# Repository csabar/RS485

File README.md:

# RS485
MAX485 breakout board which fits Arduino Pro Mini

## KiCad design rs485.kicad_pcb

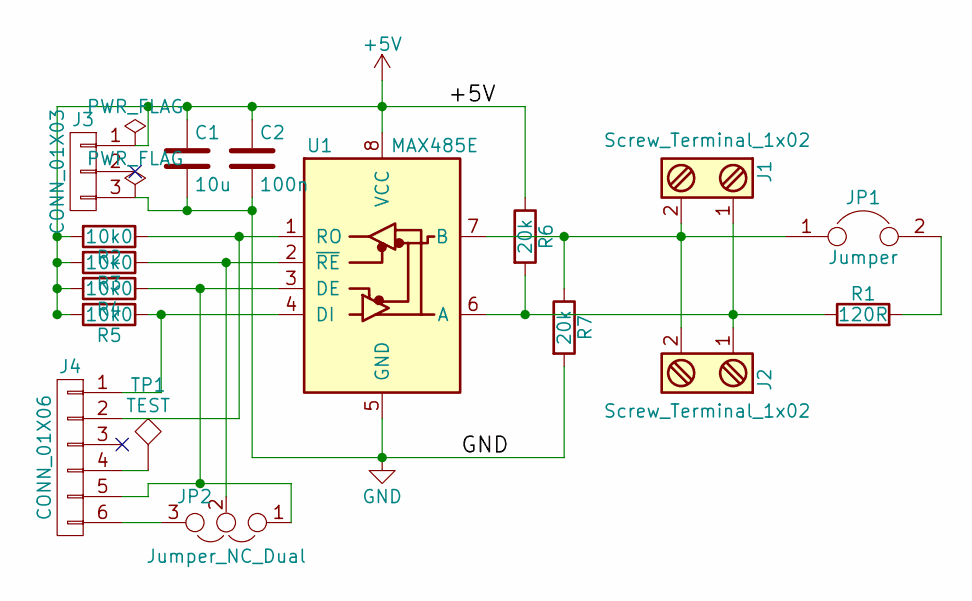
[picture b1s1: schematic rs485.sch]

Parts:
C1: 10u; C_1206
C2: 100n; C_0603
J1, J2: Screw_Terminal_1x02; TerminalBlock_Pheonix_MPT-2.54mm_2pol
J3: CONN_01X03; Pin_Header_Straight_1x03_Pitch2.54mm
J4: CONN_01X06; Pin_Header_Straight_1x06_Pitch2.54mm
JP1: Jumper; Pin_Header_Straight_1x02_Pitch2.54mm
JP2: Jumper_NC_Dual; GS3
R1: 120R; R_0603
R2, R3, R4, R5: 10k0; R_0603
R6, R7: 20k; R_0603
TP1: TEST; Measurement_Point_Round-SMD-Pad_Small
U1: MAX485E; SOIC-8_3.9x4.9mm_Pitch1.27mm

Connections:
+5V: C1.1, C2.1, J3.1, R2.2, R3.2, R4.2, R5.2, R6.1, U1.8 (VCC)
GND: C1.2, C2.2, J3.3, R7.2, U1.5 (GND)
unnamed: J1.1, J2.1, R1.1, R6.2, U1.6 (A)
unnamed: J1.2, J2.2, JP1.1, R7.1, U1.7 (B)
unnamed: J4.1, R5.1, U1.4 (DI)
unnamed: J4.2, R2.1, U1.1 (RO)
unnamed: J4.4, TP1.1
unnamed: J4.5, JP2.1, R4.1, U1.3 (DE)
unnamed: J4.6, JP2.3
unnamed: JP1.2, R1.2
unnamed: JP2.2, R3.1, U1.2 (~RE)

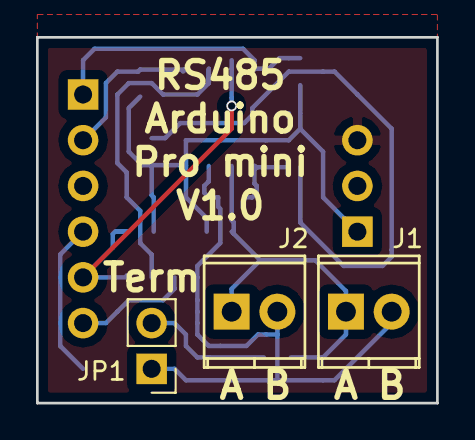
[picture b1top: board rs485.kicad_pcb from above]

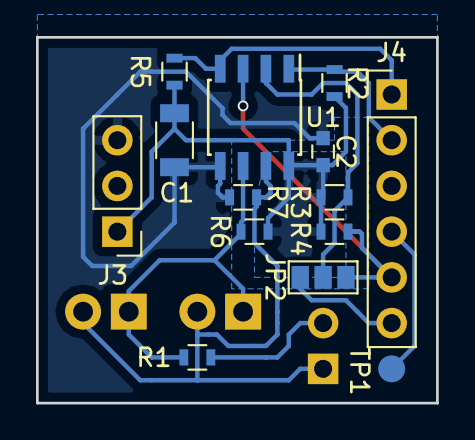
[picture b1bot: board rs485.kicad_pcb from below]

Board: 2 copper layers, 22.2 x 20.3 mm, 17 parts (14 on the bottom side), 11 nets.

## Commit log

2017-08-27 First version
2017-08-27 Added to silkscreen: +5V, GND
2017-08-28 Added OSHW logo, pin descriptions, changed version
2017-08-28 Changed BOM
2017-08-28 images
